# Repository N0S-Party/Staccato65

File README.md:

# Staccato65

[![CC BY-NC-SA 4.0][cc-by-nc-sa-shield]][cc-by-nc-sa]

A 65% board with OLED, rotary encoder support, and a 3D printed case.

**Specs:** 
* 3D printed case (top mounted)
* rotary encoder support
* OLED screen
* ATMega32u4 as microcontroller
* USB C connector (with USB 2.0)
* choice of a stepped caps lock
* hot-swappable (if I don't end up cutting costs!)

**Design goals:**
* separated arrow keys
* 1.5u alt & ctrl keys with 1.75u shift
* aesthetically pleasing through-hole diode layout on the front layer

Basically the layout will be similar to the Satisfaction75 and ID80, but without the function row. 
I also really like the look of the Discipline keyboards, so the layout of the diodes will somewhat try to reflect that. 

One of my current concerns is that the firmware size might end up too big, since I'll have to use QMK's I2C and roatry encoder libraries in addition to multiple keyboard layouts -- 
but I guess we'll see once we get there.

## Update 8/1
I started building the key matrix in the schematic. I originally wanted the schematic matrix to have a 1-to-1 mapping to the keyboard layout. 
It's actually done that way for the schematic of the Discipline, making it easy to route the traces for the PCB, and organize the layout even pre-PCB design.
Unfortunately, it ended up being 15 columns by 6 rows for me. 
This was far too many pins to support for the ATmega32u4 since I need to save some pins to support the rotary encoder and OLED. 
I'm also planning to save the SCK, MOSI and MISO pins for ISP usage, in case I ever want to set fuse bits 
(though I'm willing to give these pins up if desperate measures need to be in play).

## Update 8/4
Modified the matrix to now use 10 columns and 7 rows. This allows for a maximum of 69 switches and 1 rotary encoder switch. With the rotary encoder and OLED screen added, this oleaves the microcontroller with only one GPIO pin available (which means I *could* turn this into a 75% keyboard). I did come across [mr.keeb's PCB generator](https://builder.mrkeebs.com), but for some reason there is a bug that messes up the layout if you use a non-standard matrix; Can't say I'm not happy, since this means that my previous work wasn't all for nothing. I'm planning on using Kailh hot-swap sockets, but I might undo this if I find that it's too costly. 

## Update 8/6
Got to making the key layout on the PCB. I'm thankful I have a spare top plate and a caliper to help me confirm my switch placement. A modification I made from my initial plan is that I'm now using the "columns" in the schematics as rows. I need about 14 keys per row, and have 7 keys per column in the schematic makes that transform easy. I'll now have two disjoint traces per row on the PCB. Also, I can't get that damn encoder footprint to be centered... I'll leave that for next time.

## Update 8/12
I haven't updated here in a while, but that doesn't mean I haven't been working hard! I've finally managed to finish routing the PCB to a degree that I'm satisfied with. I might have to work a bit more on making the top right routing better, but I'd say the key routing was not too shabby. Fun fact, using Kicad 5.0.2 makes routing a pain. Traces never consistently "stuck" to each other the way I wanted it to. Thankfully, Kicad 5.1.6 was way more route-friendly. Unfortunately I couldn't really group the traces into fours that were aligned with the diode groups since some of the rows contained five switches instead of four. Nevertheless, clean routing was still possible and it still looks good as long as you don't look at it too hard. See below for pictures (you can see what I was talking about with the schematic matrix not being entirely 1-to-1 in dimension to the keyboard).

PCB and Schematics pictured are outdated. Please see the repo files for the updated versions

## Update 12/5
Okay, I don't know if anyone was following this project, but while it did seem like I had a long hiatus, I was actually working quite a bit behind the scenes. 
With the help of Sagar, and another friend of ours, we managed to get the first few prototypes out. Many revisions had to be done with the case due to 3D printing tolerances and the limitations of a 3D printer. Another issue that was caught was that the PCB plate cutout for the spacebar stabilizer was actually facing the wrong way. Unfortunately I only found this out after I got the first batch delivered, so I just had to file down the troublesome cutout by a few milimeters. Ordering from JLC PCB, the cumulative costs of PCB + plate + parts is about 70 dollars, assuming you order a batch of 10. Surprisingly, we managed to get a small groupbuy going and will be making 10 keyboards for us and a few other friends. In terms of regrets, I maybe should have opted to pay for assembly costs from the fab as well, since soldering a keyboard takes about 4 hours total. But hey, I'm really good at drag soldering now at least. As for actual release, I'm not too confident in my PCB design skills yet to release a product to members of the community. If I ever had to refine this design for a round 2, I'd probably add ESD protection, fix the plate and also make some of the footprint placements nicer. Overall, I plan to make a macropad as my next project. The reasoning is so I could try out more experimental features that I've had in mind while keeping the risk low. We also hope to make a case out of metal, which may be a challenge in itself. 

This work is licensed under a
[Creative Commons Attribution-NonCommercial-ShareAlike 4.0 International License][cc-by-nc-sa].

[![CC BY-NC-SA 4.0][cc-by-nc-sa-image]][cc-by-nc-sa]

[cc-by-nc-sa]: http://creativecommons.org/licenses/by-nc-sa/4.0/
[cc-by-nc-sa-image]: https://licensebuttons.net/l/by-nc-sa/4.0/88x31.png
[cc-by-nc-sa-shield]: https://img.shields.io/badge/License-CC%20BY--NC--SA%204.0-lightgrey.svg

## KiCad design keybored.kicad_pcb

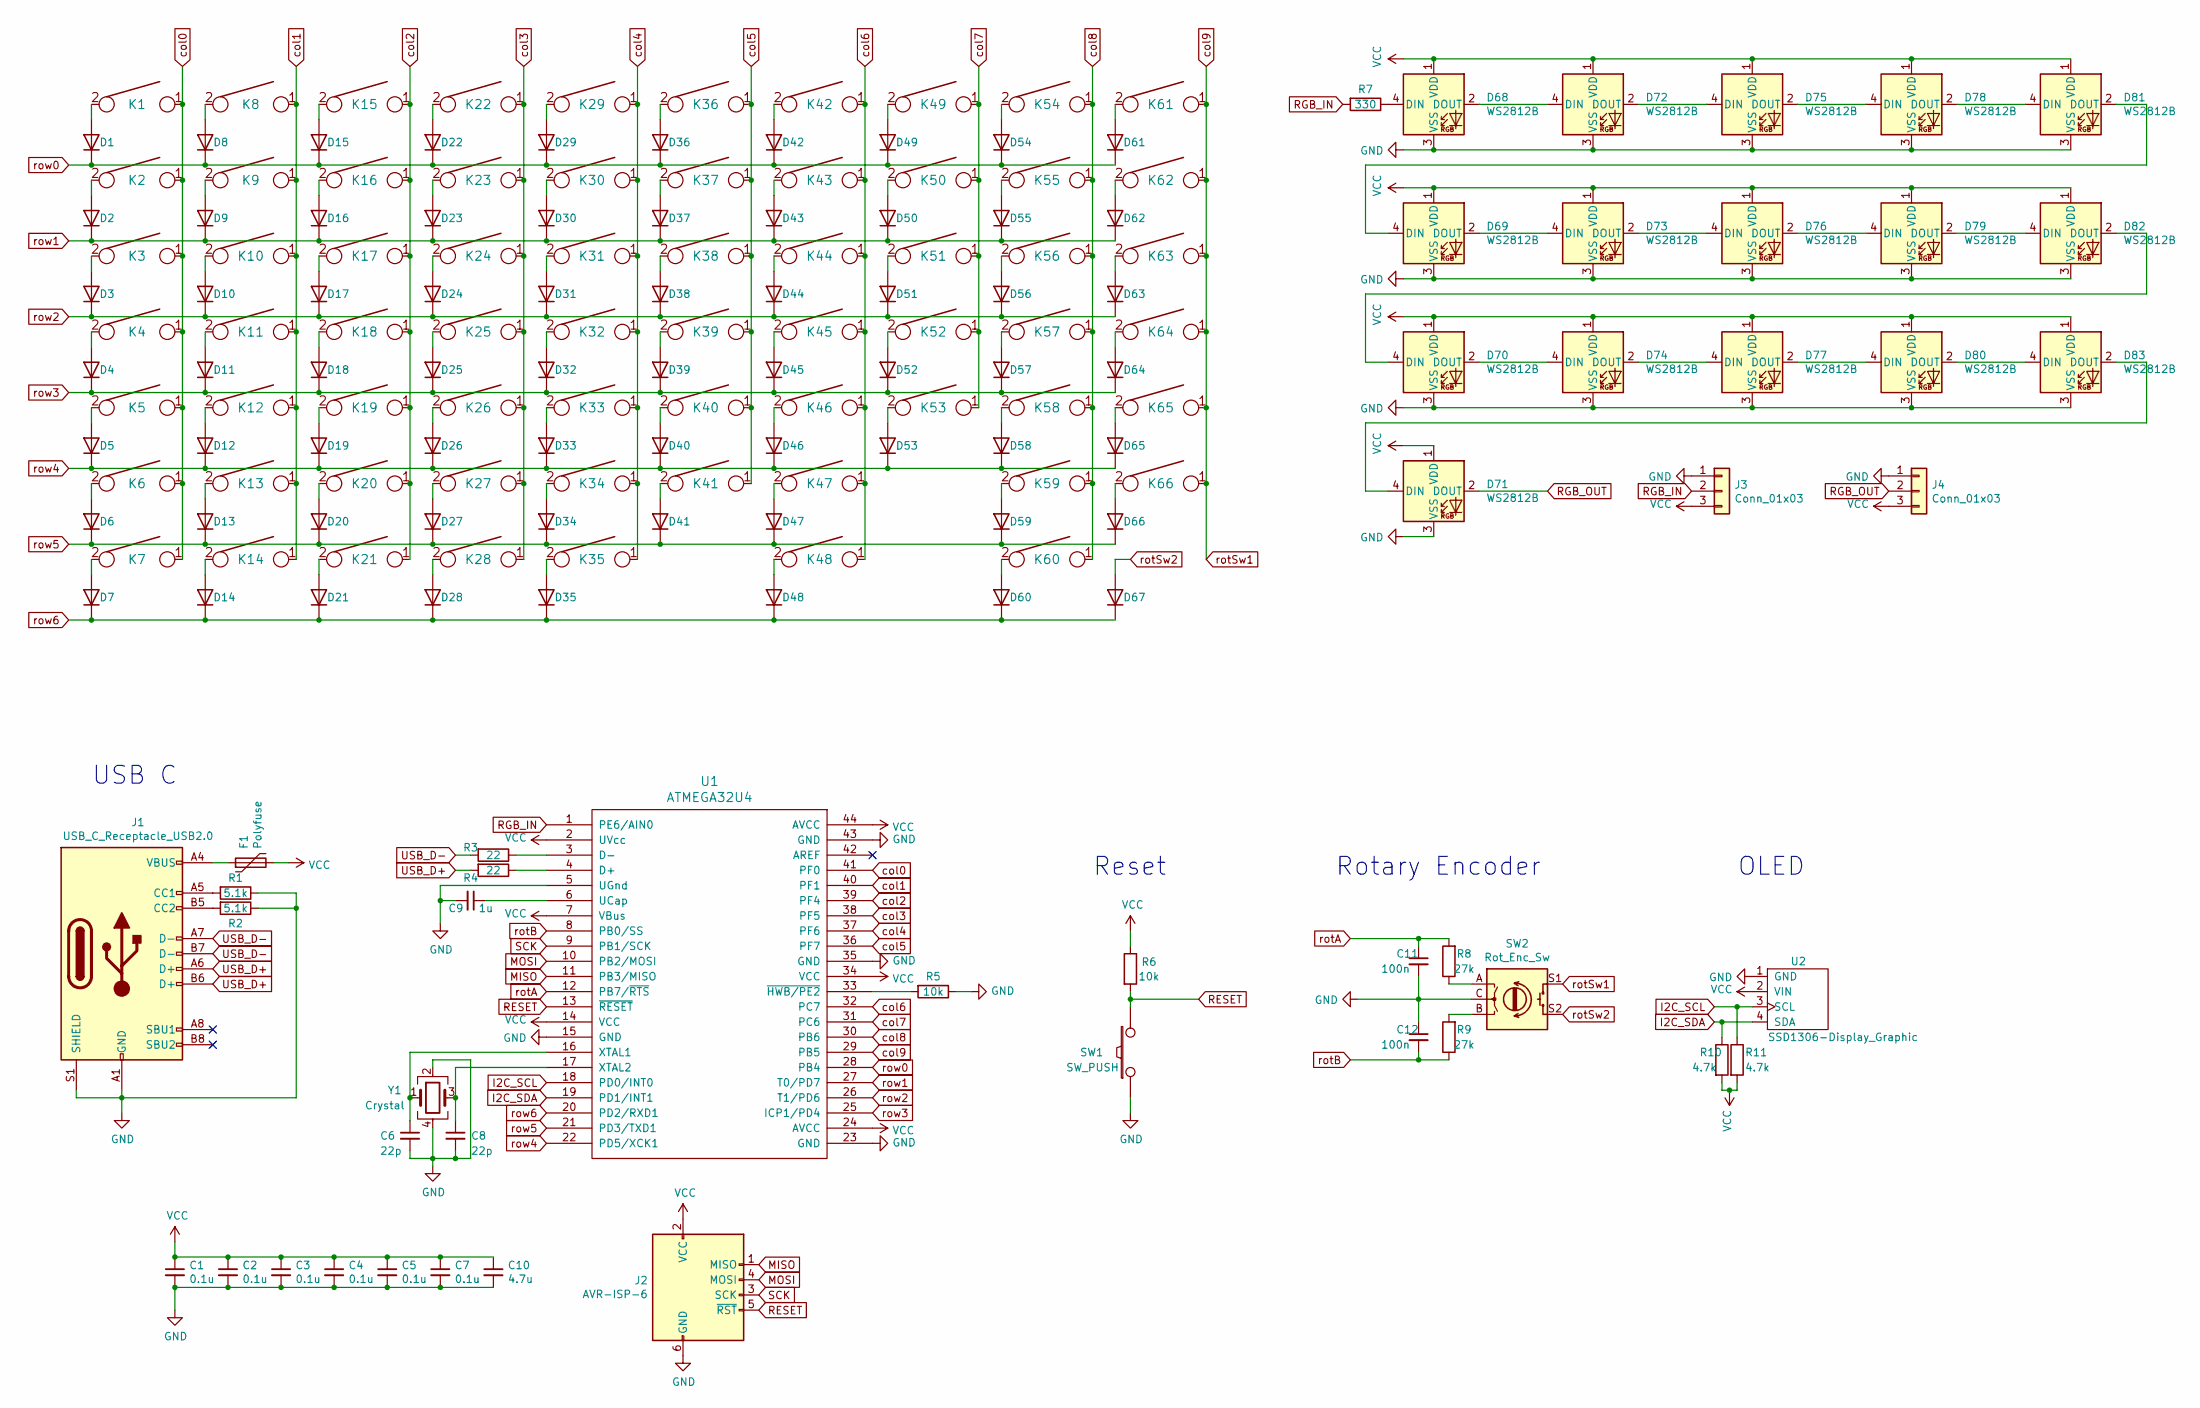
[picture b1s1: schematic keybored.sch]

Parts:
C1, C2, C3, C4, C5, C7: 0.1u; C_0805_2012Metric_Pad1.15x1.40mm_HandSolder
C6, C8: 22p; C_0805_2012Metric_Pad1.15x1.40mm_HandSolder
C9: 1u; C_0805_2012Metric_Pad1.15x1.40mm_HandSolder
C10: 4.7u; C_0805_2012Metric_Pad1.15x1.40mm_HandSolder
C11, C12: 100n; C_0805_2012Metric_Pad1.15x1.40mm_HandSolder
D1, D2, D3, D4, D5, D6, D7, D8, D9, D10, D11, D12, D13, D14, D15, D16, D17, D18, D19, D20, D21, D22, D23, D24, D25, D26, D27, D28, D29, D30, D31, D32, D33, D34, D35, D36, D37, D38, D39, D40, D41, D42, D43, D44, D45, D46, D47, D48, D49, D50, D51, D52, D53, D54, D55, D56, D57, D58, D59, D60, D61, D62, D63, D64, D65, D66, D67: D; DO-35_SOD27_5.08mm
D68, D69, D70, D71, D72, D73, D74, D75, D76, D77, D78, D79, D80, D81, D82, D83: WS2812B; LED_WS2812B_PLCC4_5.0x5.0mm_P3.2mm
F1: Polyfuse
J1: USB_C_Receptacle_USB2.0; USB_C_GCT_USB4085
J2: AVR-ISP-6; PinHeader_2x03_P2.54mm_Vertical
J3, J4: Conn_01x03; PinHeader_1x03_P2.54mm_Vertical
K1, K2, K3, K4, K5, K6, K7, K8, K9, K10, K11, K12, K13, K14, K15, K16, K17, K18, K19, K20, K21, K22, K23, K24, K25, K26, K27, K28, K29, K30, K31, K32, K33, K34, K35, K36, K37, K38, K39, K40, K41, K42, K43, K44, K45, K46, K47, K48, K49, K50, K51, K52, K53, K54, K55, K56, K57, K58, K59, K60, K61, K62, K63, K64, K65, K66: KEYSW; Kailh_socket_MX_optional
R1, R2: 5.1k; R_0805_2012Metric_Pad1.15x1.40mm_HandSolder
R3, R4: 22; R_0805_2012Metric_Pad1.15x1.40mm_HandSolder
R5, R6: 10k; R_0805_2012Metric_Pad1.15x1.40mm_HandSolder
R7: 330; R_0805_2012Metric_Pad1.15x1.40mm_HandSolder
R8, R9: 27k; R_0805_2012Metric_Pad1.15x1.40mm_HandSolder
R10, R11: 4.7k; R_0805_2012Metric_Pad1.15x1.40mm_HandSolder
SW1: SW_PUSH; SW_SPST_TL3342
SW2: Rot_Enc_Sw; RotaryEncoder_Alps_EC11E-Switch_Vertical_H20mm
U1: ATMEGA32U4; TQFP-44_10x10mm_P0.8mm
U2: SSD1306-Display_Graphic; SSD1306_OLED_128x32_0.91_inch
Y1: Crystal; Crystal_SMD_SeikoEpson_FA238-4Pin_3.2x2.5mm_HandSoldering

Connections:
GND: C1.2, C2.2, C3.2, C4.2, C5.2, C6.2, C7.2, C8.2, C9.2, C10.2, C11.2, C12.1, D68.3 (VSS), D69.3 (VSS), D70.3 (VSS), D71.3 (VSS), D72.3 (VSS), D73.3 (VSS), D74.3 (VSS), D75.3 (VSS), D76.3 (VSS), D77.3 (VSS), D78.3 (VSS), D79.3 (VSS), D80.3 (VSS), D81.3 (VSS), D82.3 (VSS), D83.3 (VSS), J1.A1 (GND), J1.A12 (GND), J1.B1 (GND), J1.B12 (GND), J1.S1 (SHIELD), J2.6 (GND), J3.1, J4.1, R1.1, R2.1, R5.1, SW1.1, SW2.C, U1.5 (UGnd), U1.15 (GND), U1.23 (GND), U1.35 (GND), U1.43 (GND), U2.1 (GND), Y1.2, Y1.4
I2C_SCL: R11.1, U1.18 (PD0/INT0), U2.3 (SCL)
I2C_SDA: R10.1, U1.19 (PD1/INT1), U2.4 (SDA)
MISO: J2.1 (MISO), U1.11 (PB3/MISO)
MOSI: J2.4 (MOSI), U1.10 (PB2/MOSI)
unnamed: C6.1, U1.16 (XTAL1), Y1.1
unnamed: C8.1, U1.17 (XTAL2), Y1.3
unnamed: C9.1, U1.6 (UCap)
unnamed: D1.2 (A), K1.2
unnamed: D2.2 (A), K2.2
unnamed: D3.2 (A), K3.2
unnamed: D4.2 (A), K4.2
unnamed: D5.2 (A), K5.2
unnamed: D6.2 (A), K6.2
unnamed: D7.2 (A), K7.2
unnamed: D8.2 (A), K8.2
unnamed: D9.2 (A), K9.2
unnamed: D10.2 (A), K10.2
unnamed: D11.2 (A), K11.2
unnamed: D12.2 (A), K12.2
unnamed: D13.2 (A), K13.2
unnamed: D14.2 (A), K14.2
unnamed: D15.2 (A), K15.2
unnamed: D16.2 (A), K16.2
unnamed: D17.2 (A), K17.2
unnamed: D18.2 (A), K18.2
unnamed: D19.2 (A), K19.2
unnamed: D20.2 (A), K20.2
unnamed: D21.2 (A), K21.2
unnamed: D22.2 (A), K22.2
unnamed: D23.2 (A), K23.2
unnamed: D24.2 (A), K24.2
unnamed: D25.2 (A), K25.2
unnamed: D26.2 (A), K26.2
unnamed: D27.2 (A), K27.2
unnamed: D28.2 (A), K28.2
unnamed: D29.2 (A), K29.2
unnamed: D30.2 (A), K30.2
unnamed: D31.2 (A), K31.2
unnamed: D32.2 (A), K32.2
unnamed: D33.2 (A), K33.2
unnamed: D34.2 (A), K34.2
unnamed: D35.2 (A), K35.2
unnamed: D36.2 (A), K36.2
unnamed: D37.2 (A), K37.2
unnamed: D38.2 (A), K38.2
unnamed: D39.2 (A), K39.2
unnamed: D40.2 (A), K40.2
unnamed: D41.2 (A), K41.2
unnamed: D42.2 (A), K42.2
unnamed: D43.2 (A), K43.2
unnamed: D44.2 (A), K44.2
unnamed: D45.2 (A), K45.2
unnamed: D46.2 (A), K46.2
unnamed: D47.2 (A), K47.2
unnamed: D48.2 (A), K48.2
unnamed: D49.2 (A), K49.2
unnamed: D50.2 (A), K50.2
unnamed: D51.2 (A), K51.2
unnamed: D52.2 (A), K52.2
unnamed: D53.2 (A), K53.2
unnamed: D54.2 (A), K54.2
unnamed: D55.2 (A), K55.2
unnamed: D56.2 (A), K56.2
unnamed: D57.2 (A), K57.2
unnamed: D58.2 (A), K58.2
unnamed: D59.2 (A), K59.2
unnamed: D60.2 (A), K60.2
unnamed: D61.2 (A), K61.2
unnamed: D62.2 (A), K62.2
unnamed: D63.2 (A), K63.2
unnamed: D64.2 (A), K64.2
unnamed: D65.2 (A), K65.2
unnamed: D66.2 (A), K66.2
unnamed: D68.2 (DOUT), D72.4 (DIN)
unnamed: D68.4 (DIN), R7.1
unnamed: D69.2 (DOUT), D73.4 (DIN)
unnamed: D69.4 (DIN), D81.2 (DOUT)
unnamed: D70.2 (DOUT), D74.4 (DIN)
unnamed: D70.4 (DIN), D82.2 (DOUT)
unnamed: D71.4 (DIN), D83.2 (DOUT)
unnamed: D72.2 (DOUT), D75.4 (DIN)
unnamed: D73.2 (DOUT), D76.4 (DIN)
unnamed: D74.2 (DOUT), D77.4 (DIN)
unnamed: D75.2 (DOUT), D78.4 (DIN)
unnamed: D76.2 (DOUT), D79.4 (DIN)
unnamed: D77.2 (DOUT), D80.4 (DIN)
unnamed: D78.2 (DOUT), D81.4 (DIN)
unnamed: D79.2 (DOUT), D82.4 (DIN)
unnamed: D80.2 (DOUT), D83.4 (DIN)
unnamed: J1.A5 (CC1), R1.2
unnamed: J1.B5 (CC2), R2.2
unnamed: R3.1, U1.3 (D-)
unnamed: R4.1, U1.4 (D+)
unnamed: R5.2, U1.33 (~HWB/PE2)
unnamed: R8.1, SW2.A
unnamed: R9.2, SW2.B
RESET: J2.5 (~RST), R6.2, SW1.2, U1.13 (~RESET)
RGB_IN: J3.2, R7.2, U1.1 (PE6/AIN0)
RGB_OUT: D71.2 (DOUT), J4.2
SCK: J2.3 (SCK), U1.9 (PB1/SCK)
USB_D+: J1.A6 (D+), J1.B6 (D+), R4.2
USB_D-: J1.A7 (D-), J1.B7 (D-), R3.2
col0: K1.1, K2.1, K3.1, K4.1, K5.1, K6.1, K7.1, U1.41 (PF0)
col1: K8.1, K9.1, K10.1, K11.1, K12.1, K13.1, K14.1, U1.40 (PF1)
col2: K15.1, K16.1, K17.1, K18.1, K19.1, K20.1, K21.1, U1.39 (PF4)
col3: K22.1, K23.1, K24.1, K25.1, K26.1, K27.1, K28.1, U1.38 (PF5)
col4: K29.1, K30.1, K31.1, K32.1, K33.1, K34.1, K35.1, U1.37 (PF6)
col5: K36.1, K37.1, K38.1, K39.1, K40.1, K41.1, U1.36 (PF7)
col6: K42.1, K43.1, K44.1, K45.1, K46.1, K47.1, K48.1, U1.32 (PC7)
col7: K49.1, K50.1, K51.1, K52.1, K53.1, U1.31 (PC6)
col8: K54.1, K55.1, K56.1, K57.1, K58.1, K59.1, K60.1, U1.30 (PB6)
col9: K61.1, K62.1, K63.1, K64.1, K65.1, K66.1, SW2.S1, U1.29 (PB5)
rotA: C11.1, R8.2, U1.12 (PB7/~RTS)
rotB: C12.2, R9.1, U1.8 (PB0/SS)
rotSw2: D67.2 (A), SW2.S2
row0: D1.1 (K), D8.1 (K), D15.1 (K), D22.1 (K), D29.1 (K), D36.1 (K), D42.1 (K), D49.1 (K), D54.1 (K), D61.1 (K), U1.28 (PB4)
row1: D2.1 (K), D9.1 (K), D16.1 (K), D23.1 (K), D30.1 (K), D37.1 (K), D43.1 (K), D50.1 (K), D55.1 (K), D62.1 (K), U1.27 (T0/PD7)
row2: D3.1 (K), D10.1 (K), D17.1 (K), D24.1 (K), D31.1 (K), D38.1 (K), D44.1 (K), D51.1 (K), D56.1 (K), D63.1 (K), U1.26 (T1/PD6)
row3: D4.1 (K), D11.1 (K), D18.1 (K), D25.1 (K), D32.1 (K), D39.1 (K), D45.1 (K), D52.1 (K), D57.1 (K), D64.1 (K), U1.25 (ICP1/PD4)
row4: D5.1 (K), D12.1 (K), D19.1 (K), D26.1 (K), D33.1 (K), D40.1 (K), D46.1 (K), D53.1 (K), D58.1 (K), D65.1 (K), U1.22 (PD5/XCK1)
row5: D6.1 (K), D13.1 (K), D20.1 (K), D27.1 (K), D34.1 (K), D41.1 (K), D47.1 (K), D59.1 (K), D66.1 (K), U1.21 (PD3/TXD1)
row6: D7.1 (K), D14.1 (K), D21.1 (K), D28.1 (K), D35.1 (K), D48.1 (K), D60.1 (K), D67.1 (K), U1.20 (PD2/RXD1)

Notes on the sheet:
Reset
Rotary Encoder
OLED
USB C

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
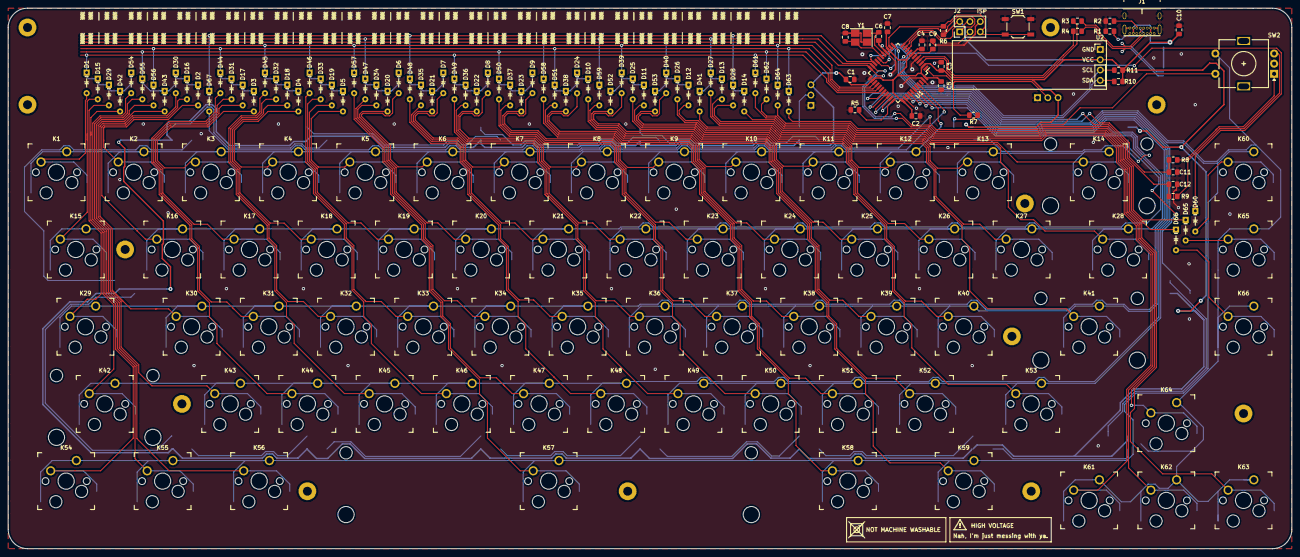
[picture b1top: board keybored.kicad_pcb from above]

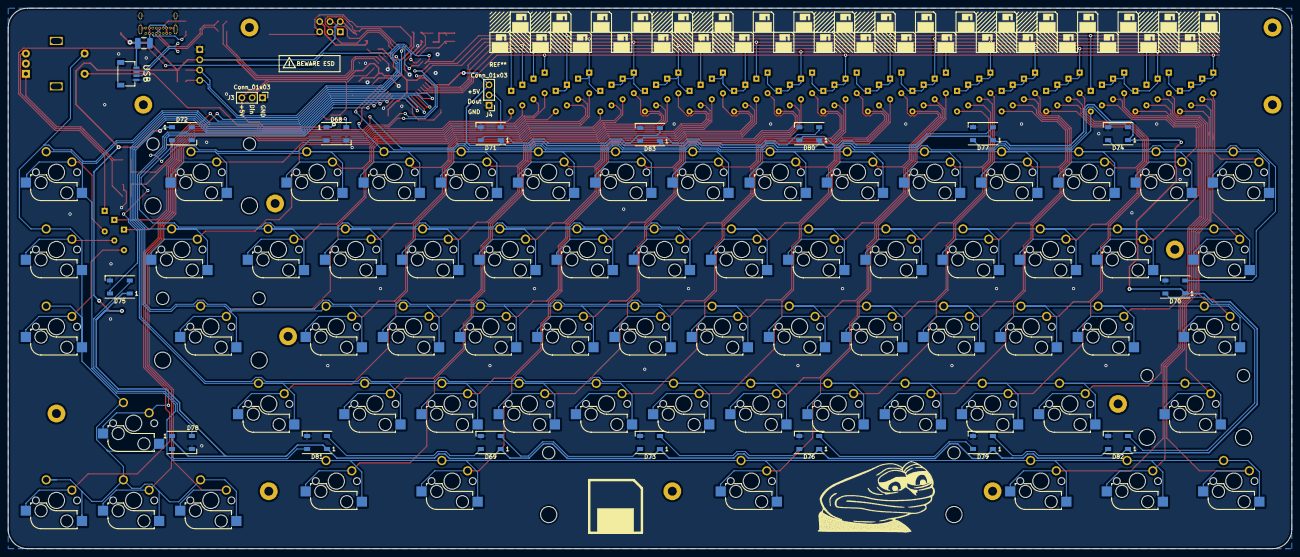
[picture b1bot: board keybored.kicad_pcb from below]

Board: 2 copper layers, 316.7 x 133.3 mm, 181 parts (18 on the bottom side), 124 nets.

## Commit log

2020-08-01 Create README
    - added update
    - added planned specs and design goals
2020-08-01 Added Schematic
    - USB, reset implemented
    - matrix pinouts still WIP
2020-08-04 Designations and footprints assigned
    - added component references + footprints
    - started PCB design
    - added rotary encoder and OLED
2020-08-04 Update for README
2020-08-06 Key layout done
2020-08-10 Diode layout and row routing
2020-08-13 Finished PCB routing rev 1
2020-08-13 Added images of PCB and schematic
2020-08-13 Updated README, added images
2020-08-13 Updated PCB image
2020-08-13 Fix typo in README
2020-08-19 Major pcb changes
    - now uses a dual footprint for switches
    - added ARGB support
    - added stabilizer holes
    - added header pin support for ISP
2020-09-15 Add plate, updates to PCB
2020-09-15 Actually add the plate files this time
2020-09-16 add 3d files to source control
2020-09-16 add led underglow
2020-09-16 first render
2020-09-18 split case into 3d printable stls, add a gitignore
2020-09-27 Updates to PCB + Plate
    - plate dimensions fixed
    - cutouts for stabilizers added
    - spacebar stabilizer holes added to PCB
    - moved RGB LEDs on PCB
2020-09-27 Added License
    Pls no steal. Thank
2020-09-27 Added license link to readme
2020-09-27 Actually add the license to README
2020-09-27 Final touches on PCB and Plate
    - added decals and memes on PCB + plate
    - copper fill added for plate
    - final commit before prototype order
2020-12-05 Updates to keyboard PCB and Plate
2020-12-05 Update README.md
    - added update and real prototype images
